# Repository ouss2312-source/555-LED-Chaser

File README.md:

# 555-LED-Chaser
i made it through hack club
if you want the tutorial, you can see https://blueprint.hackclub.com/starter-projects/blinky

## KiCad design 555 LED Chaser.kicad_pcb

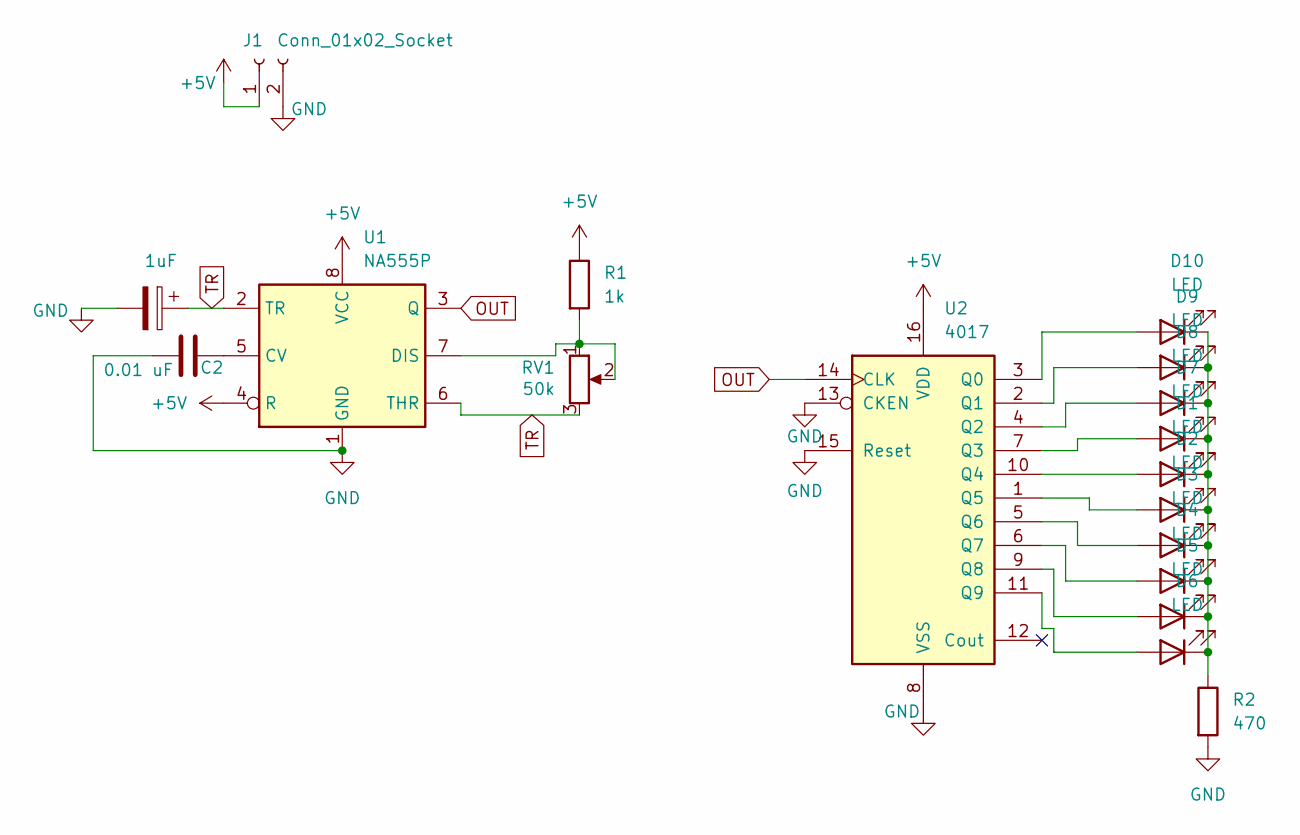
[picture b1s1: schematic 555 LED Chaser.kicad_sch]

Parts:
C1: 1uF; CP_Radial_D5.0mm_P2.00mm
C2: 0.01 uF; C_Disc_D5.0mm_W2.5mm_P5.00mm
D1, D2, D3, D4, D5, D6, D7, D8, D9, D10: LED; LED_D5.0mm
J1: Conn_01x02_Socket; PinSocket_1x02_P2.54mm_Vertical
R1: 1k; R_Axial_DIN0207_L6.3mm_D2.5mm_P7.62mm_Horizontal
R2: 470; R_Axial_DIN0207_L6.3mm_D2.5mm_P7.62mm_Horizontal
RV1: 50k; Potentiometer_Bourns_3386W_Horizontal
U1: NA555P; DIP-8_W7.62mm
U2: 4017; DIP-16_W7.62mm

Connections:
+5V: J1.1, R1.1, U1.4 (R), U1.8 (VCC), U2.16 (VDD)
GND: C1.2, C2.1, J1.2, R2.2, U1.1 (GND), U2.8 (VSS), U2.13 (CKEN), U2.15 (Reset)
unnamed: D1.2 (A), U2.10 (Q4)
unnamed: D1.1 (K), D2.1 (K), D3.1 (K), D4.1 (K), D5.1 (K), D6.1 (K), D7.1 (K), D8.1 (K), D9.1 (K), D10.1 (K), R2.1
unnamed: D2.2 (A), U2.1 (Q5)
unnamed: D3.2 (A), U2.5 (Q6)
unnamed: D4.2 (A), U2.6 (Q7)
unnamed: D5.2 (A), U2.9 (Q8)
unnamed: D6.2 (A), U2.11 (Q9)
unnamed: D7.2 (A), U2.7 (Q3)
unnamed: D8.2 (A), U2.4 (Q2)
unnamed: D9.2 (A), U2.2 (Q1)
unnamed: D10.2 (A), U2.3 (Q0)
unnamed: C2.2, U1.5 (CV)
unnamed: R1.2, RV1.1, RV1.2, U1.7 (DIS)
OUT: U1.3 (Q), U2.14 (CLK)
TR: C1.1, RV1.3, U1.2 (TR), U1.6 (THR)

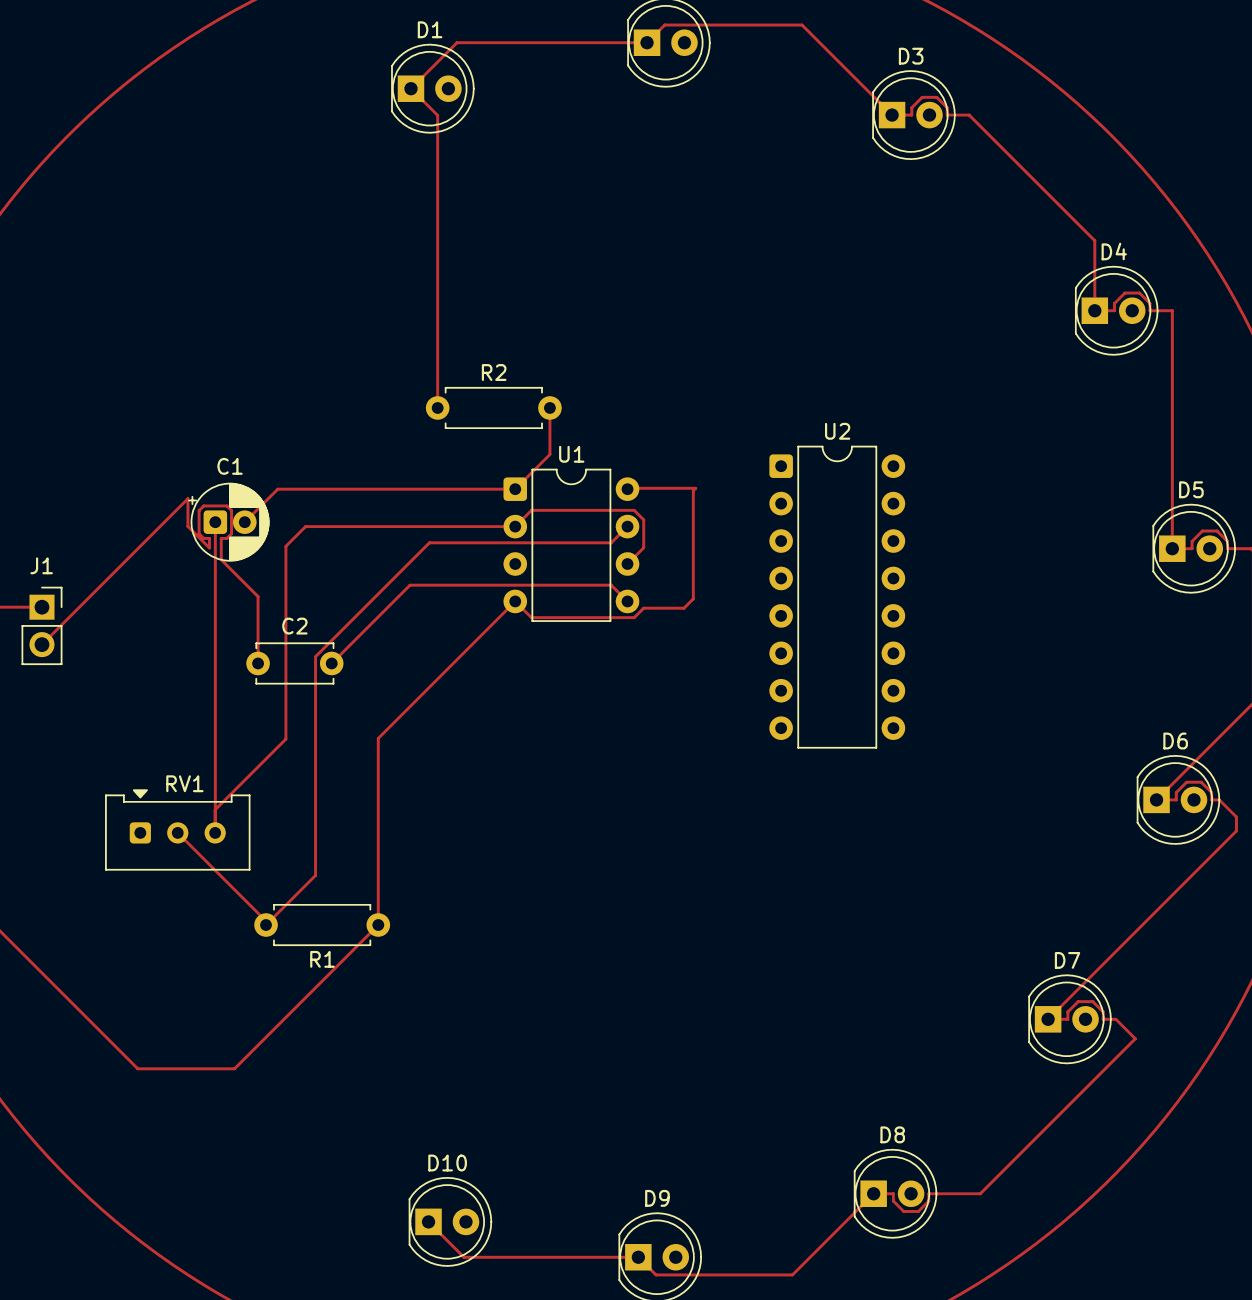
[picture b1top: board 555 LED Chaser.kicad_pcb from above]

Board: 2 copper layers, 18 parts (0 on the bottom side), 17 nets.

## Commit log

2026-02-19 Add image upload placeholder to README
2026-02-19 Remove image upload placeholder from README
2026-02-19 Add tutorial link to README
